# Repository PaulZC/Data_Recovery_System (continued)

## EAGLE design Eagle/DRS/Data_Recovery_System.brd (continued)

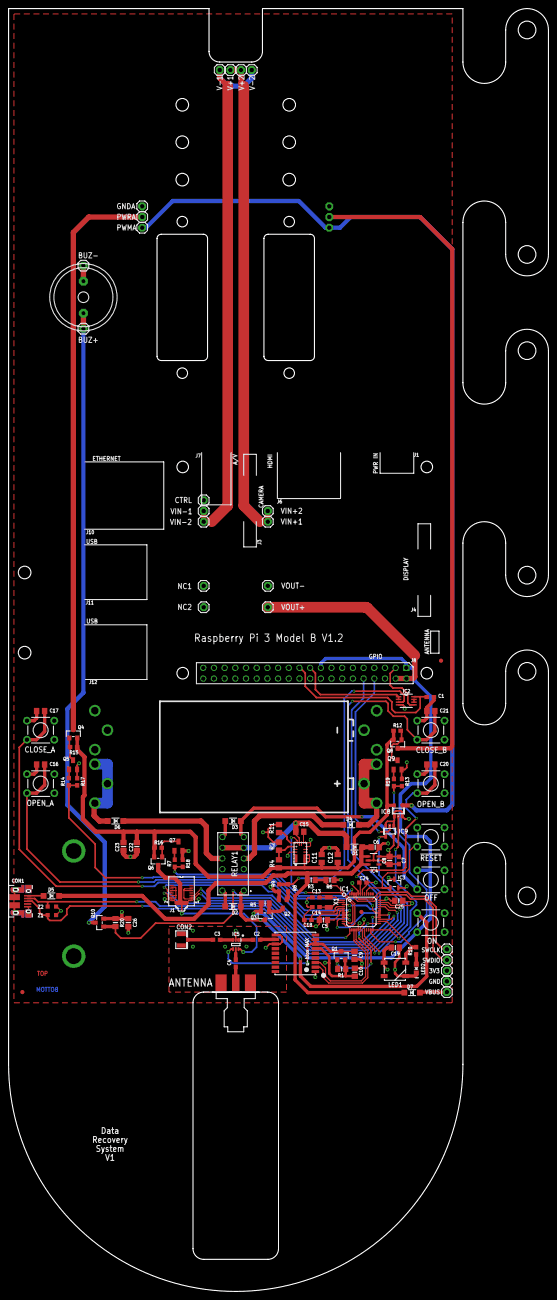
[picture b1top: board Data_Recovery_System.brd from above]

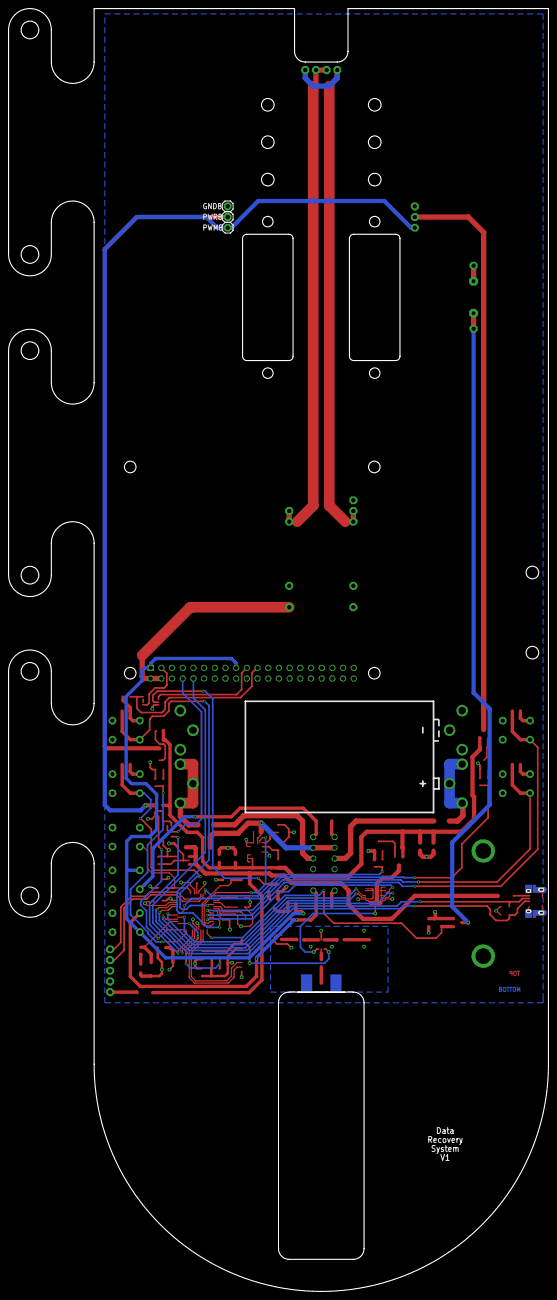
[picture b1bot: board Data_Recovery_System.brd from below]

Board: 4 copper layers, 128.3 x 304.8 mm, 123 parts (4 on the bottom side), 76 nets.

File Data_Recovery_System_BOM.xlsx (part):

Part | X | Y | Angle | Package | Value | Manufacturer | Manufacturer Part No | Farnell Part No | Mouser Part No | McMaster Part No | Description | Alternative Part
Dimensions | 107.95 | 304.80 |  |  |  |  |  |  |  |  | Excludes snap-off servo linkage pieces
Fiducials - for solder paste mask alignment:
FD1 | 3.28 | 71.12 | 0 |  |  |  |  |  |  |  | Fiducial 1mm
FD2 | 102.75 | 149.86000000000001 | 0 |  |  |  |  |  |  |  | Fiducial 1mm
Surface Mount Components:
C1 | 100.2 | 141.22 | 0 | 0603 | 1uF | Walsin | 0603X105K100CT | 2496916 |  |  | MultiLayer Ceramic Capacitor; 1uF; 10V; 0603; X5R | 1uF 50V ±10% 0603 Samsung
C2 | 58.93 | 83.57 | 0 | 0603 | 120pF | Walsin | 0603B121K500CT | 2524820 |  |  | MultiLayer Ceramic Capacitor; 120pF; 50V; 0603
C3 | 49.4 | 83.57 | 180 | 0603 | 120pF | Walsin | 0603B121K500CT | 2524820 |  |  | MultiLayer Ceramic Capacitor; 120pF; 50V; 0603
C4 | 53.98 | 77.98 | 90 | 0603 | 120pF | Walsin | 0603B121K500CT | 2524820 |  |  | MultiLayer Ceramic Capacitor; 120pF; 50V; 0603
C5 | 74.8 | 88.27 | 180 | 0805 | 0.1uF | Walsin | 0805B104K500CT | 2496944 |  |  | MultiLayer Ceramic Capacitor; 0.1uF; 50V; 0805; X7R | 100nF 50V ±10% 0805 Samsung
C6 | 87.1 | 105.54 | 0 | 0805 | 10uF | Walsin | 0805F106Z100CT | 2496998 |  |  | MultiLayer Ceramic Capacitor; 10uF; 10V; 0805 | 10uF 16V ±10% 0805 Samsung
C7 | 92.75 | 102.39 | 270 | 0603 | 1uF | Walsin | 0603X105K100CT | 2496916 |  |  | MultiLayer Ceramic Capacitor; 1uF; 10V; 0603; X5R | 1uF 50V ±10% 0603 Samsung
C8 | 90.53 | 102.39 | 270 | 0805 | 10uF | Walsin | 0805F106Z100CT | 2496998 |  |  | MultiLayer Ceramic Capacitor; 10uF; 10V; 0805 | 10uF 16V ±10% 0805 Samsung
C9 | 82.2 | 79.86 | 270 | 0805 | 0.1uF | Walsin | 0805B104K500CT | 2496944 |  |  | MultiLayer Ceramic Capacitor; 0.1uF; 50V; 0805; X7R | 100nF 50V ±10% 0805 Samsung
C10 | 82.26 | 75.84 | 90 | 0805 | 10uF | Walsin | 0805F106Z100CT | 2496998 |  |  | MultiLayer Ceramic Capacitor; 10uF; 10V; 0805 | 10uF 16V ±10% 0805 Samsung
C11 | 74.400000000000006 | 102.87 | 90 | 0805 | 10nF | Walsin | 0805B103K500CT | 2496939 |  |  | MultiLayer Ceramic Capacitor; 10nF; 50V; 0805; X7R | 10nF 50V ±5% 0805 Samsung
C12 | 78.209999999999994 | 102.87 | 90 | 0805 | 10uF | Walsin | 0805F106Z100CT | 2496998 |  |  | MultiLayer Ceramic Capacitor; 10uF; 10V; 0805 | 10uF 16V ±10% 0805 Samsung
C13 | 73.03 | 93.6 | 180 | 0603 | 12pF | Walsin | 0603N120J500CT | 2496884 |  |  | MultiLayer Ceramic Capacitor; 12pF; 50V; 0603 | 12pF 50V ±5% 0603 Samsung
C14 | 73.03 | 91.31 | 180 | 0603 | 12pF | Walsin | 0603N120J500CT | 2496884 |  |  | MultiLayer Ceramic Capacitor; 12pF; 50V; 0603 | 12pF 50V ±5% 0603 Samsung
C15 | 69.19 | 109.22 | 0 | 0805 | 10uF | Walsin | 0805F106Z100CT | 2496998 |  |  | MultiLayer Ceramic Capacitor; 10uF; 10V; 0805 | 10uF 16V ±10% 0805 Samsung
C16 | 7.62 | 125.2 | 0 | 0805 | 10nF | Walsin | 0805B103K500CT | 2496939 |  |  | MultiLayer Ceramic Capacitor; 10nF; 50V; 0805; X7R | 10nF 50V ±5% 0805 Samsung
C17 | 7.62 | 137.9 | 0 | 0805 | 10nF | Walsin | 0805B103K500CT | 2496939 |  |  | MultiLayer Ceramic Capacitor; 10nF; 50V; 0805; X7R | 10nF 50V ±5% 0805 Samsung
C18 | 71.12 | 88.27 | 180 | 0603 | 1uF | Walsin | 0603X105K100CT | 2496916 |  |  | MultiLayer Ceramic Capacitor; 1uF; 10V; 0603; X5R | 1uF 50V ±10% 0603 Samsung
C19 | 91.89 | 81.69 | 0 | 0805 | 10uF | Walsin | 0805F106Z100CT | 2496998 |  |  | MultiLayer Ceramic Capacitor; 10uF; 10V; 0805 | 10uF 16V ±10% 0805 Samsung
C20 | 100.33 | 125.2 | 0 | 0805 | 10nF | Walsin | 0805B103K500CT | 2496939 |  |  | MultiLayer Ceramic Capacitor; 10nF; 50V; 0805; X7R | 10nF 50V ±5% 0805 Samsung
C21 | 100.33 | 137.9 | 0 | 0805 | 10nF | Walsin | 0805B103K500CT | 2496939 |  |  | MultiLayer Ceramic Capacitor; 10nF; 50V; 0805; X7R | 10nF 50V ±5% 0805 Samsung
C22 | 30.48 | 105.69 | 270 | 0805 | 10uF | Walsin | 0805F106Z100CT | 2496998 |  |  | MultiLayer Ceramic Capacitor; 10uF; 10V; 0805 | 10uF 16V ±10% 0805 Samsung
C23 | 27.3 | 105.69 | 270 | 0805 | 0.1uF | Walsin | 0805B104K500CT | 2496944 |  |  | MultiLayer Ceramic Capacitor; 0.1uF; 50V; 0805; X7R | 100nF 50V ±10% 0805 Samsung
C24 | 84.2 | 97.16 | 0 | 0603 | 1uF | Walsin | 0603X105K100CT | 2496916 |  |  | MultiLayer Ceramic Capacitor; 1uF; 10V; 0603; X5R | 1uF 50V ±10% 0603 Samsung
C25 | 92.71 | 92.84 | 0 | 0805 | 10uF | Walsin | 0805F106Z100CT | 2496998 |  |  | MultiLayer Ceramic Capacitor; 10uF; 10V; 0805 | 10uF 16V ±10% 0805 Samsung
C26 | 28.45 | 87.63 | 270 | 0805 | 10uF | Walsin | 0805F106Z100CT | 2496998 |  |  | MultiLayer Ceramic Capacitor; 10uF; 10V; 0805 | 10uF 16V ±10% 0805 Samsung
CON1 | 2.99 | 92.71 | 270 |  | Micro_USB | Amphenol_FCI | 10103594 | 2293752 |  |  | Amphenol FCI 10103594 Micro USB Type B | A01SB7X4X1B21-167 Micro USB 5S B
CON2 | 41.78 | 83.57 | 0 | uFL | uFL | Hirose | U.FL-R-SMT(01) | 3908021 |  |  | HIROSE U.FL-R-SMT(01); U.FL Coaxial; Straight Jack; 50 ohm
D1 | 82.18 | 105.57 | 180 | SOD-123 | MBR120 | ON SEMICONDUCTOR | MBR120VLSFT1G | 1431044 |  |  | Schottky Rectifier; 20V; 1A; SOD-123
D2 | 53.34 | 91.44 | 180 | SOD-123 | MBR120 | ON SEMICONDUCTOR | MBR120VLSFT1G | 1431044 |  |  | Schottky Rectifier; 20V; 1A; SOD-123
D3 | 53.34 | 111.76 | 180 | SOD-123 | MBR120 | ON SEMICONDUCTOR | MBR120VLSFT1G | 1431044 |  |  | Schottky Rectifier; 20V; 1A; SOD-123
D4 | 81.41 | 110.87 | 0 | SOD-123 | MBR120 | ON SEMICONDUCTOR | MBR120VLSFT1G | 1431044 |  |  | Schottky Rectifier; 20V; 1A; SOD-123
D5 | 10.16 | 93.98 | 180 | SOD-123 | MBR120 | ON SEMICONDUCTOR | MBR120VLSFT1G | 1431044 |  |  | Schottky Rectifier; 20V; 1A; SOD-123
D6 | 25.4 | 111.76 | 180 | SOD-123 | MBR120 | ON SEMICONDUCTOR | MBR120VLSFT1G | 1431044 |  |  | Schottky Rectifier; 20V; 1A; SOD-123
D7 | 95.89 | 70.989999999999995 | 0 | SOD-123 | MBR120 | ON SEMICONDUCTOR | MBR120VLSFT1G | 1431044 |  |  | Schottky Rectifier; 20V; 1A; SOD-123
IC1 | 83.82 | 90.17 | 0 | TQFP48-7X7 | SAMD21G18A-AFT | Atmel / Microchip | SAMD21G18A-AFT |  | 556-ATSAMD21G18A-AFT
IC2 | 94.49 | 140.34 | 0 | SOP65P400X130-8N | SN74LVC2G02DCTR | Texas Instruments | SN74LVC2G02DCTR | 1236358 |  |  | NOR Gate, 2 Input, 32 mA, 1.65 V to 5.5 V, SSOP-8
IC3 | 91.66 | 96.91 | 0 | SOT23-3 | MCP111T-240E/TT | Microchip | MCP111T-240E/TT | 1627192 |  |  | Reset Supervisor; SOT23-3; 2.40V; Open Drain; Active Low
IC4 | 86.72 | 102.39 | 270 | SOT23-5 | SPX3819-3.3 | Exar | SPX3819M5-L-3-3/TR |  | 701-SPX3819M5-L-33TR |  | LDO Voltage Regulator; 500mA; SOT-23-5
IC5 | 53.98 | 82.42 | 270 | SOT65P220X100-6N | AS179-92LF | Skyworks Solutions | AS179-92LF | 1753762 | 873-AS179-92LF |  | Skyworks AS179-92LF RF Switch
IC6 | 68.150000000000006 | 80.34 | 0 |  | MAX-M8Q | u-blox | MAX-M8Q |  |  |  | https://www.u-blox.com/en/product/max-m8-series
IC7 | 69.319999999999993 | 104.32 | 0 | QFN-20 | MPM3610 | MPS | MPM3610AGQV-P |  | 946-MPM3610AGQV-P |  | Switching Voltage Regulator; 21V; 1.2A; DC/DC
IC8 | 92.61 | 114.18 | 0 | SOT23-5 | 74AHCT1G125DBV | Texas Instruments | SN74AHCT1G125DBVR | 1105927 |  |  | Buffer / Line Driver; Single Gate
IC9 | 90.55 | 109.34 | 180 | SOT23-5 | 74AHCT1G125DBV | Texas Instruments | SN74AHCT1G125DBVR | 1105927 |  |  | Buffer / Line Driver; Single Gate
J1 | 41.09 | 94.65 | 270 |  | SS4-10-3.50 | Samtec | SS4-10-3.50-L-D-K-TR | 2085336 |  |  | Samtec SS4-10-3.50-L-D-K-TR
LED1 | 91.8 | 76.52 | 0 |  | WS2812B | Sparkfun / Worldsemi | WS2812B |  | 474-COM-13667 |  | RGB LED with Driver
LED2 | 96.88 | 76.709999999999994 | 180 | 2.0x1.25 | RED | Wurth Electronik | 150080RS75000 | 2322077 | 710-150080RS75000 |  | LED; Red; 20mA; 2V; 2.0x1.25mm
Q1 | 79.03 | 79.8 | 0 | SOT23 | DMG3415U-7 | Diodes Inc. | DMG3415U-7 | 1843688 |  |  | MOSFET; P Channel; SOT23-WIDE
Q2 | 65.150000000000006 | 92.08 | 180 | SOT23 | 2N2222 | Fairchild | MMBT2222A | 9846700 |  |  | Bipolar (BJT) Single Transistor, NPN, 40 V, 350 mW, 1 A
Q3 | 60.96 | 89.28 | 180 | SOT23 | DMG3415U-7 | Diodes Inc. | DMG3415U-7 | 1843688 |  |  | MOSFET; P Channel; SOT23-WIDE
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
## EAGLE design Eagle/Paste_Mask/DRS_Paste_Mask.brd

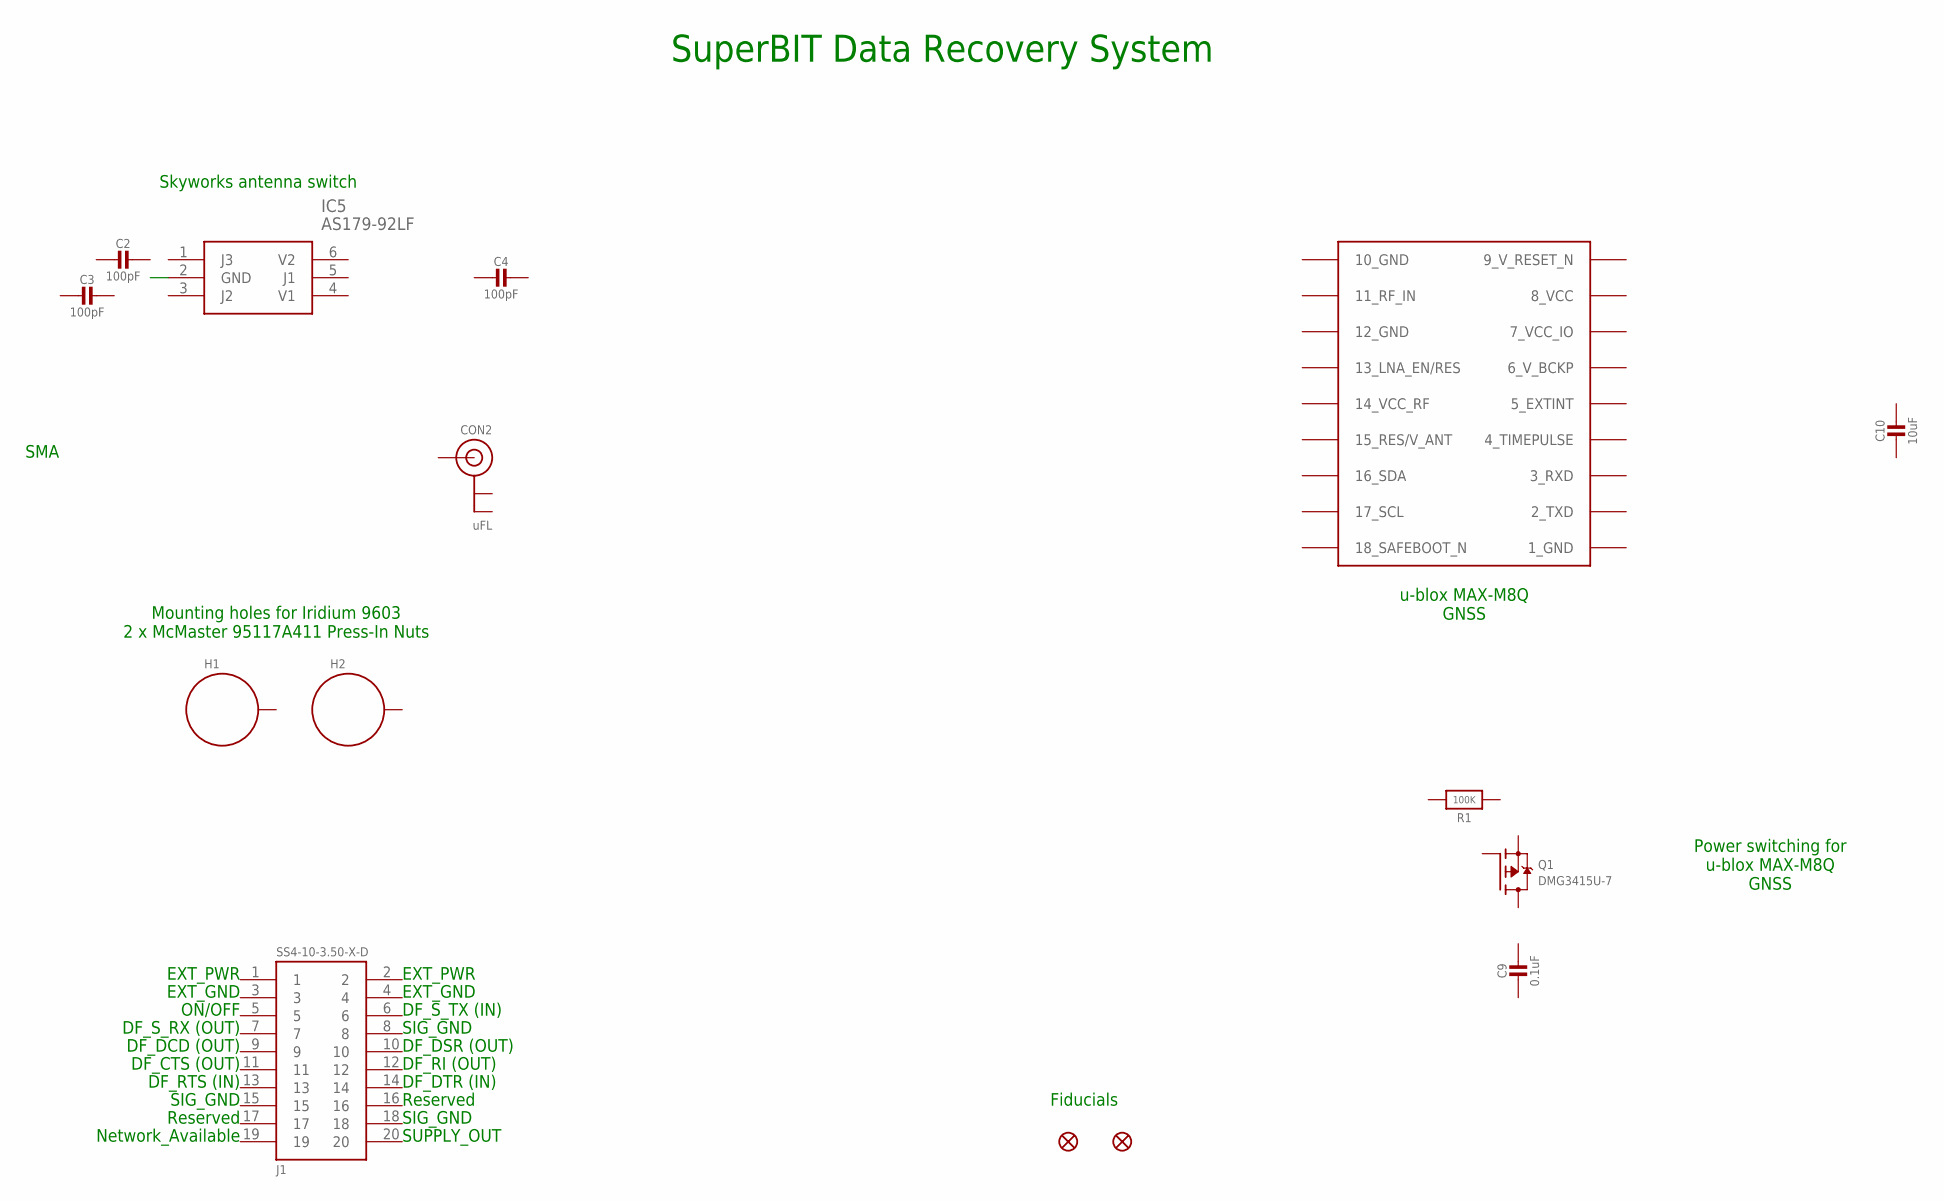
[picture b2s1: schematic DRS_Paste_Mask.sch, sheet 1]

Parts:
C2, C3, C4: 100pF; 0603-NO@1
C9: 0.1uF; 0805-NO@1
C10: 10uF; 0805-NO@1
CON2: uFL; U.FL
FD1, FD2: FIDUCIAL1X2; FIDUCIAL-1X2
H1, H2: STANDOFF_ELECTRICALMCMASTER-95117A411; STANDOFF-ELECTRICAL-MCMASTER-95117A411
IC5: AS179-92LF; SOT65P220X100-6N
IC6: MAX-M8
J1: SS4-10-3.50-X-D
Q1: DMG3415U-7; SOT23-WIDE
R1: 100K; 0805-NO

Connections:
1_GND: IC6.1_GND
7_VCC_IO: IC6.7_VCC_IO
8_VCC: IC6.8_VCC
9_V_RESET_N: IC6.9_RESET_N (9_V_RESET_N)
10_GND: IC6.10_GND
12_GND: IC6.12_GND

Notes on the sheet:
Mounting holes for Iridium 9603 2 x McMaster 95117A411 Press-In Nuts
SuperBIT Data Recovery System
EXT_PWR
EXT_GND
ON/OFF
DF_S_RX (OUT)
DF_DCD (OUT)
DF_CTS (OUT)
DF_RTS (IN)
SIG_GND
Reserved
Network_Available
DF_S_TX (IN)
DF_DSR (OUT)
DF_RI (OUT)
DF_DTR (IN)
SUPPLY_OUT
Fiducials
u-blox MAX-M8Q GNSS
Power switching for u-blox MAX-M8Q GNSS
Skyworks antenna switch
SMA

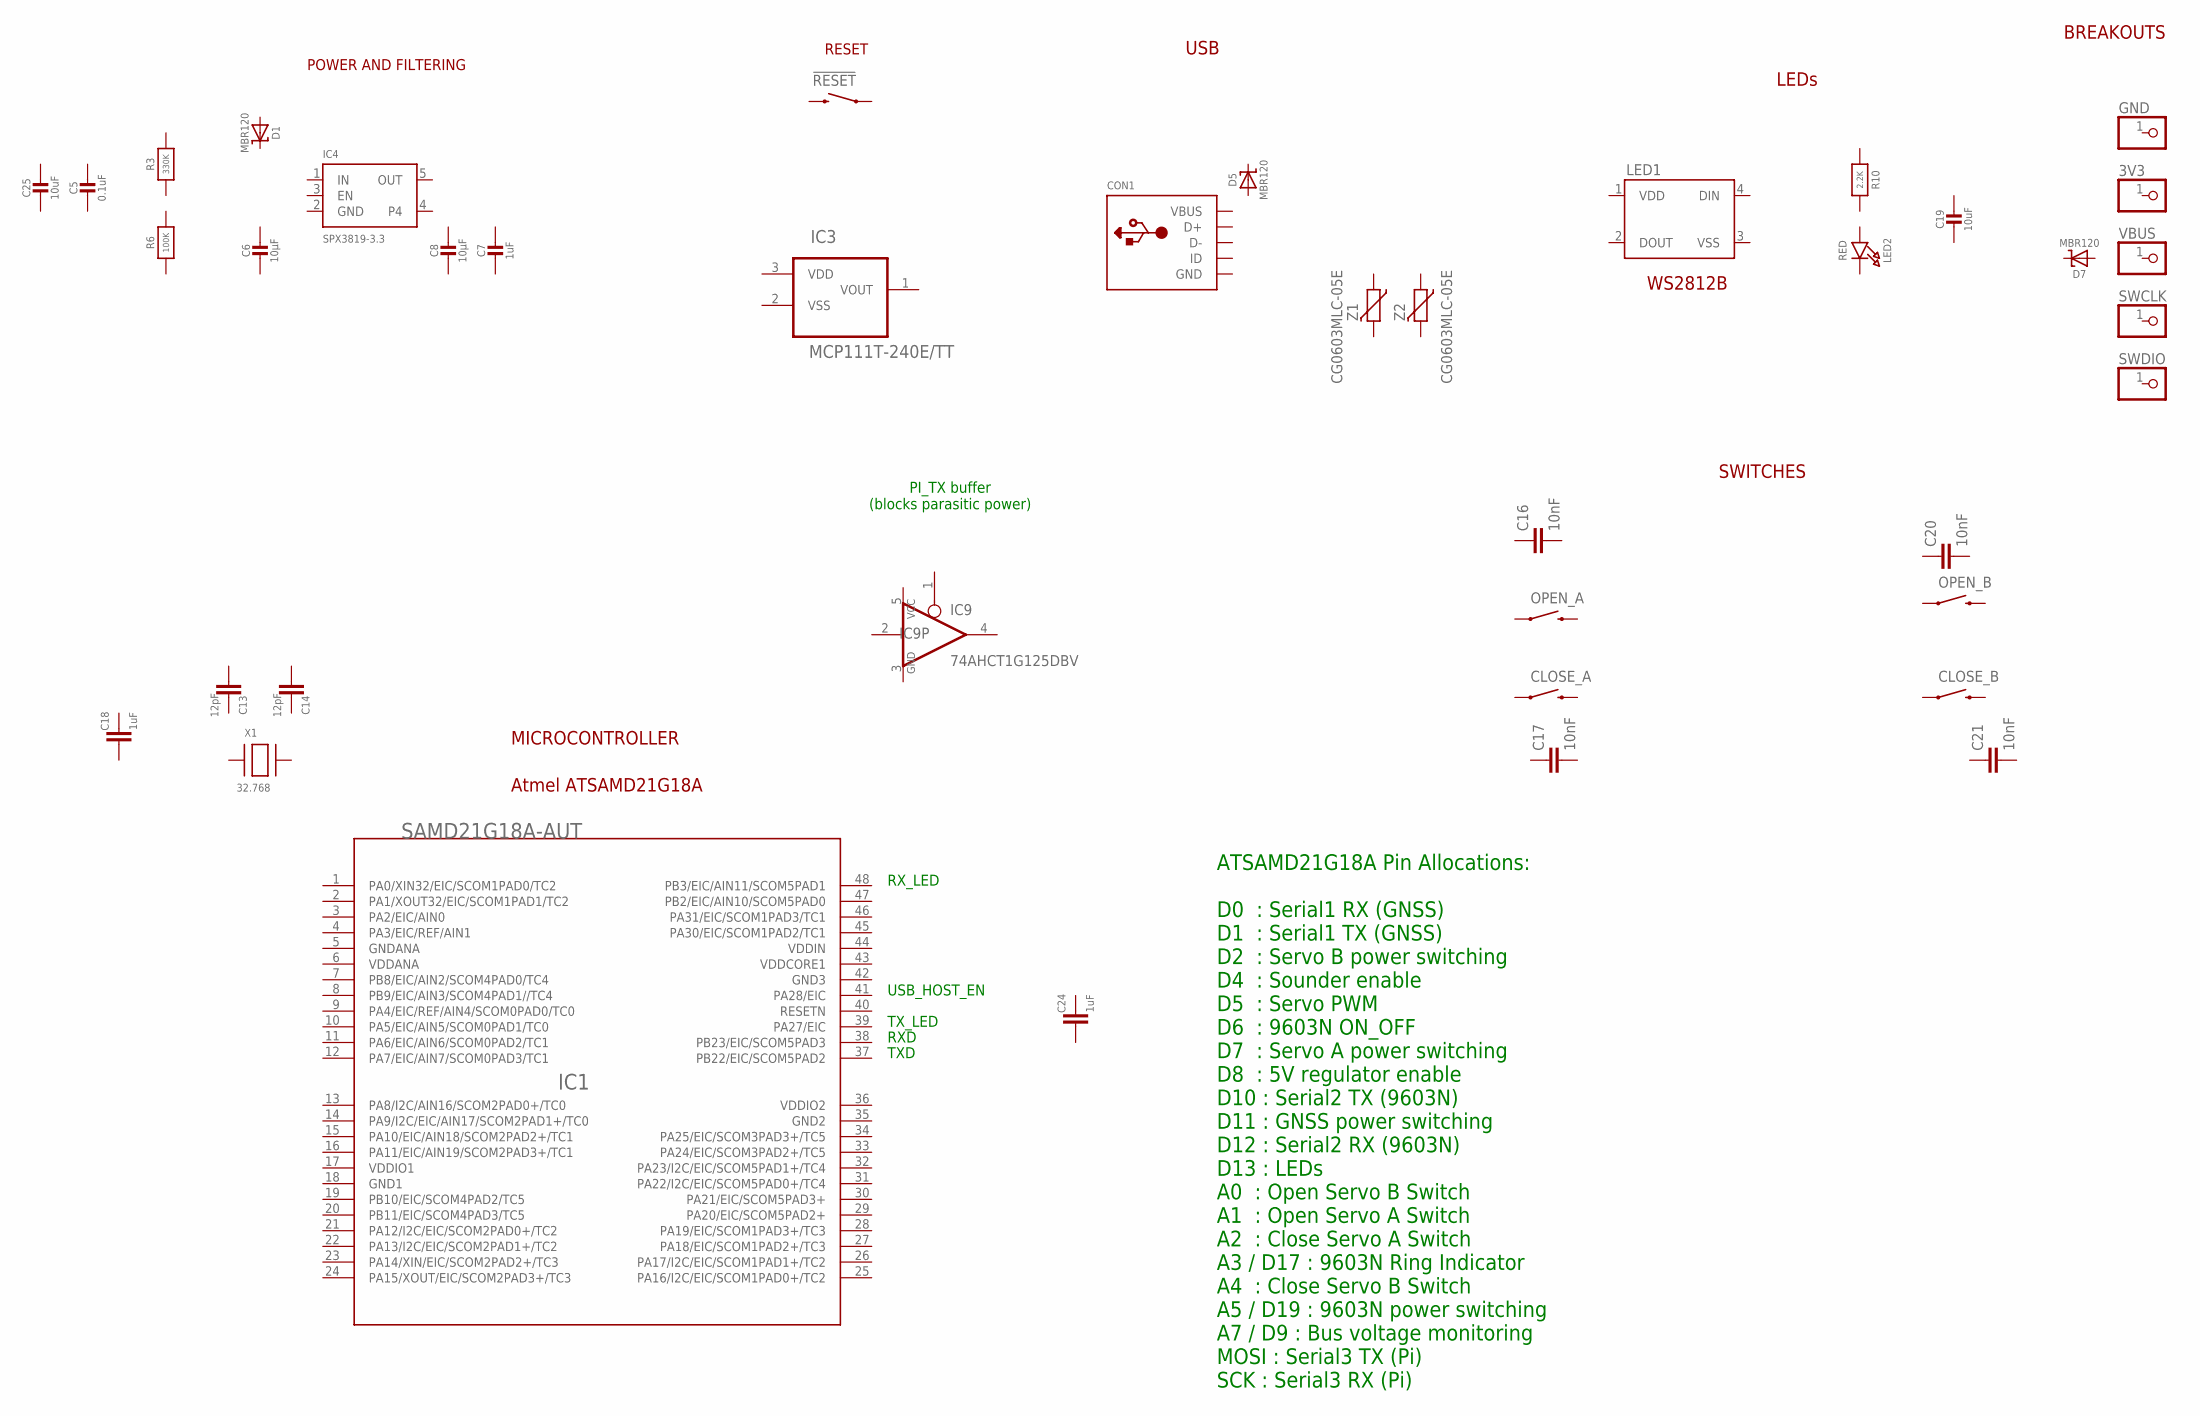
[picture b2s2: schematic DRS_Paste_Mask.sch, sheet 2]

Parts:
3V3: PINHD-1X1; 1X01
!RESET: SWITCH-MOMENTARY-2PTH; TACTILE-PTH
C5: 0.1uF; 0805-NO@1
C6, C8: 10µF; 0805-NO@1
C7: 1uF; 0603-NO@1
C13, C14: 12pF; C0603
C16, C17, C20, C21: 10nF; C0805
C18, C24: 1uF; C0603
C19, C25: 10uF; 0805-NO@1
CLOSE_A: SWITCH-MOMENTARY-2PTH; TACTILE-PTH
CLOSE_B: SWITCH-MOMENTARY-2PTH; TACTILE-PTH
CON1: MICROBUILDER_USBFCI_10103594_CORRECTED; MICROBUILDER_FCI_10103594_CORRECTED
D1, D5, D7: MBR120; SOD-123
GND: PINHD-1X1; 1X01
IC1: SAMD21G18A-AUT; TQFP48-7X7
IC3: MCP111T-240E/TT; SOT95P237X112-3N; MPN MCP111T-240E/TT
IC4: SPX3819-3.3; SOT23-5
IC9: 74AHCT1G125DBV; SOT23-5
LED1: WS2812B
LED2: RED; CHIPLED_0805_NOOUTLINE
OPEN_A: SWITCH-MOMENTARY-2PTH; TACTILE-PTH
OPEN_B: SWITCH-MOMENTARY-2PTH; TACTILE-PTH
R3: 330K; 0805-NO
R6: 100K; 0805-NO
R10: 2.2K; 0603-NO
SWCLK: PINHD-1X1; 1X01
SWDIO: PINHD-1X1; 1X01
VBUS: PINHD-1X1; 1X01
X1: 32.768; XTAL3215
Z1, Z2: CG0603MLC-05E; CT/CN0603

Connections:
GND: CON1.BASE@1 (GND), CON1.BASE@2 (GND), CON1.GND, CON1.SPRT@1 (GND), CON1.SPRT@2 (GND), CON1.SPRT@3 (GND), CON1.SPRT@4 (GND), IC4.2 (GND), IC9.3 (GND); also elsewhere on the board
GND1: IC1.18 (GND1)
GND2: IC1.35 (GND2)
GND3: IC1.42 (GND3)
GNDANA: IC1.5 (GNDANA)
IN: IC4.1 (IN)
VBUS: CON1.VBUS
VCC: IC9.5 (VCC); also elsewhere on the board
VDD: IC3.3 (VDD), LED1.1 (VDD)
VDDANA: IC1.6 (VDDANA)
VDDIN: IC1.44 (VDDIN)
VDDIO1: IC1.17 (VDDIO1)
VDDIO2: IC1.36 (VDDIO2)
VSS: IC3.2 (VSS), LED1.3 (VSS)

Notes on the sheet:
MICROCONTROLLER
USB_HOST_EN
TXD
RXD
TX_LED
RX_LED
Atmel ATSAMD21G18A
POWER AND FILTERING
RESET
USB
BREAKOUTS
LEDs
WS2812B
SWITCHES
ATSAMD21G18A Pin Allocations: D0 : Serial1 RX (GNSS) D1 : Serial1 TX (GNSS) D2 : Servo B power switching D4 : Sounder enable D5 : Servo PWM D6 : 9603N ON_OFF D7 : Servo A power switching D8 : 5V regulator enable D10 : Serial2 TX (9603N) D11 : GNSS power switching D12 : Serial2 RX (9603N) D13 : LEDs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
PI_TX buffer (blocks parasitic power)

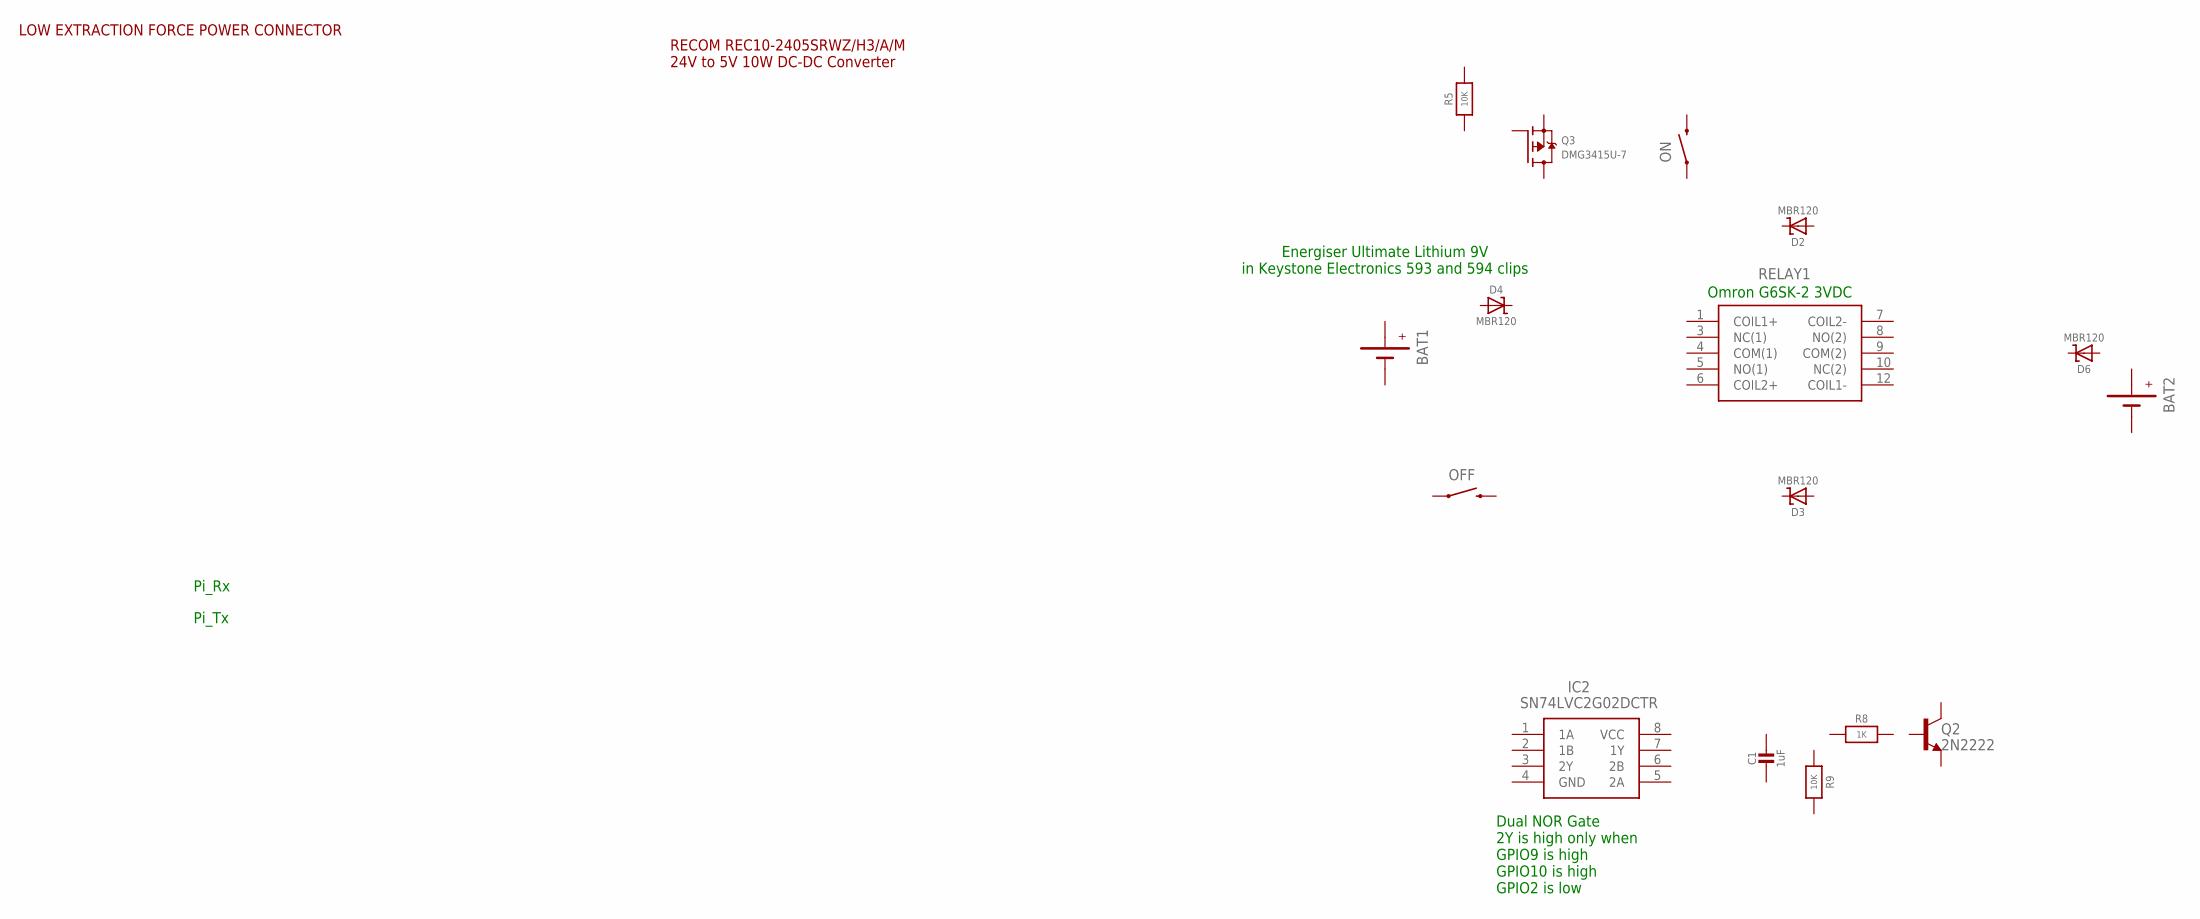
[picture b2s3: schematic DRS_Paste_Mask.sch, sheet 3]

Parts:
BAT1, BAT2: BATTERYBATTERY-9V-KEYSTONE-593-594; BATTERY-9V-KEYSTONE-593-594
C1: 1uF; 0603-NO@1
D2, D3, D4, D6: MBR120; SOD-123
IC2: SN74LVC2G02DCTR; SOP65P400X130-8N
OFF: SWITCH-MOMENTARY-2PTH; TACTILE-PTH
ON: SWITCH-MOMENTARY-2PTH; TACTILE-PTH
Q2: 2N2222; SOT23-BEC
Q3: DMG3415U-7; SOT23-WIDE
R5: 10K; 0805-NO
R8: 1K; 0603-NO
R9: 10K; 0603-NO
RELAY1: G6SK-2_DC5; G6SK2DC5

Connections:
+: BAT1.PWR (+), BAT1.PWR1 (+), BAT1.PWR2 (+), BAT2.PWR (+), BAT2.PWR1 (+), BAT2.PWR2 (+)
-: BAT1.GND (-), BAT1.GND1 (-), BAT1.GND2 (-), BAT2.GND (-), BAT2.GND1 (-), BAT2.GND2 (-)

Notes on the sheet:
Omron G6SK-2 3VDC
Energiser Ultimate Lithium 9V in Keystone Electronics 593 and 594 clips
LOW EXTRACTION FORCE POWER CONNECTOR
RECOM REC10-2405SRWZ/H3/A/M 24V to 5V 10W DC-DC Converter
Dual NOR Gate 2Y is high only when GPIO9 is high GPIO10 is high GPIO2 is low
Pi_Tx
Pi_Rx

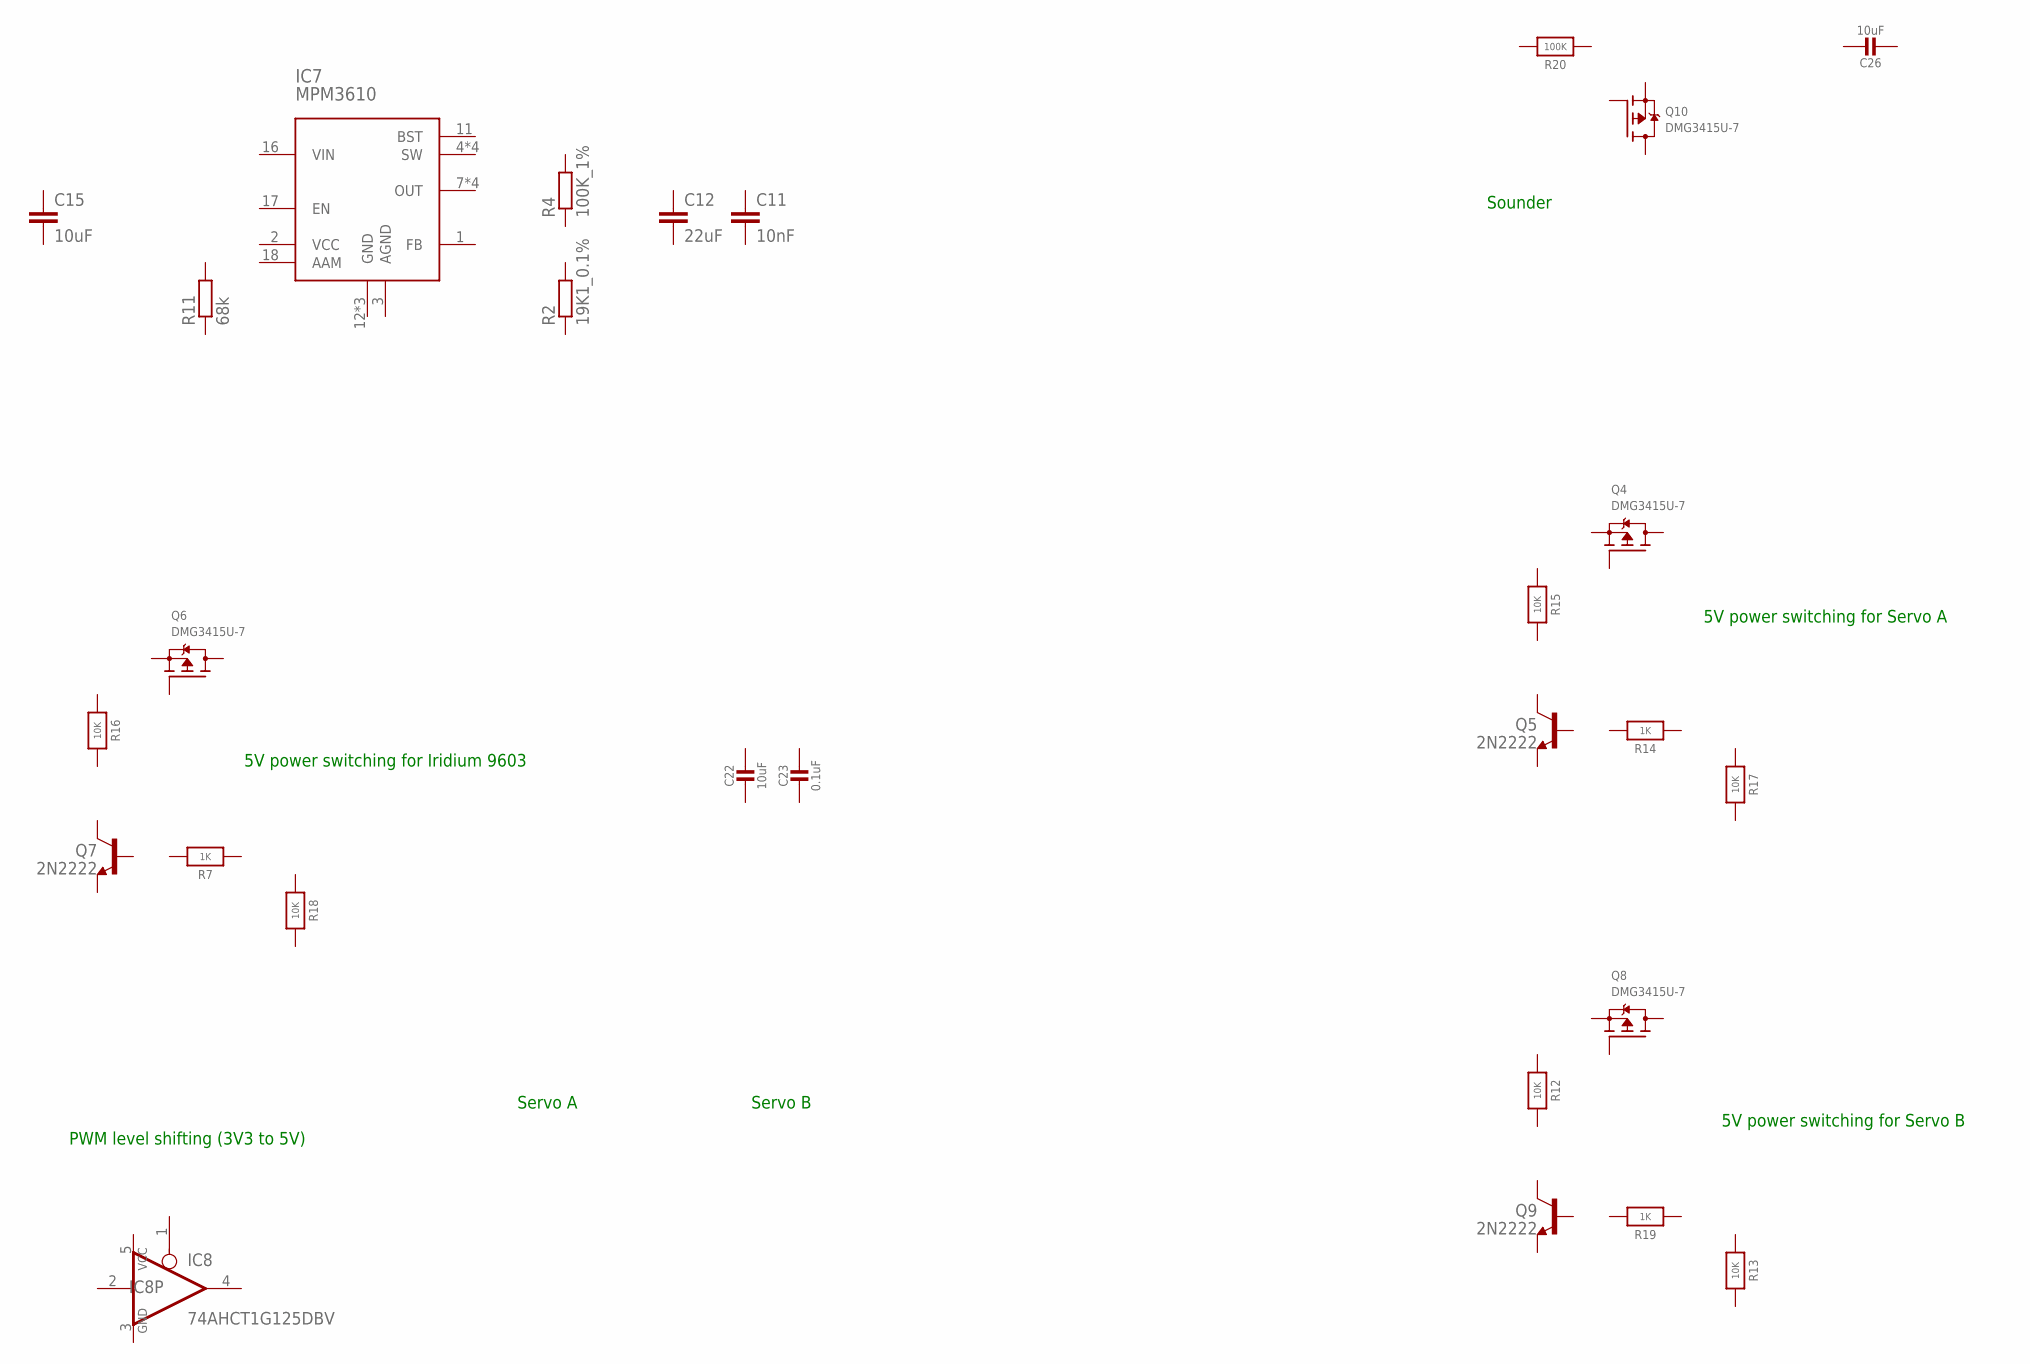
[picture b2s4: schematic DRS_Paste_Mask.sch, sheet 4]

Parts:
C11: 10nF; C0805
C12: 22uF; C0805
C15: 10uF; C0805
C22, C26: 10uF; 0805-NO@1
C23: 0.1uF; 0805-NO@1
IC7: MPM3610; QFN-20
IC8: 74AHCT1G125DBV; SOT23-5
Q4, Q6, Q8, Q10: DMG3415U-7; SOT23-WIDE
Q5, Q7, Q9: 2N2222; SOT23-BEC
R2: 19K1_0.1%; R0805
R4: 100K_1%; R0805
R7, R14, R19: 1K; 0603-NO
R11: 68k; R0805
R12, R13, R15, R16, R17, R18: 10K; 0603-NO
R20: 100K; 0805-NO

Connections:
GND: IC8.3 (GND); also elsewhere on the board
VCC: IC8.5 (VCC); also elsewhere on the board

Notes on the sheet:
Servo A
Servo B
5V power switching for Servo A
5V power switching for Servo B
5V power switching for Iridium 9603
PWM level shifting (3V3 to 5V)
Sounder

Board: 4 copper layers, 99 parts (1 on the bottom side), 6 nets, no tracks yet.

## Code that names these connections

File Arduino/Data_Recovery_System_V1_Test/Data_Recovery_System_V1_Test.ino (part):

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// D1  : Serial1 TX (GNSS)
// D2  : Servo B power switching
// D4 / PA08 / TCC1WO2 : Sounder enable
// D5 / PA15 / TCC0WO5 : Servo PWM
// D6  : 9603N ON_OFF
// D7  : Servo A power switching
// D8  : 5V regulator enable
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static const int ServoB = 2; // Servo B Enable (Pull high to enable the servo)
static const int Sounder = 4; // Sounder Enable (Pull low to enable the sounder)
const uint8_t pwmPin = 5;
static const int IridiumSleepPin = 6; // Iridium Sleep connected to D6
static const int ServoA = 7; // Servo A Enable (Pull high to enable the servo)
static const int enable5V = 8; // Enable the MPM3610 5V regulator (Pull high to enable 5V)
static const int GPS_EN = 11; // GNSS Enable on pin D11 (Pull low to enable the GNSS)
static const int ledPin = 13; // WB2812B + Red LED on pin D13
static const int openSwitchB = 14;
static const int openSwitchA = 15;
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  
  pinMode(pwmPin, OUTPUT); // Redundant?

  //pinMode(IridiumSleepPin, OUTPUT); // Iridium 9603N Sleep Pin
  //digitalWrite(IridiumSleepPin, LOW); // Disable the Iridium 9603
  pinMode(ringIndicator, INPUT); // Define an input for the Iridium 9603 Ring Indicator

  pixels.begin(); // This initializes the NeoPixel library.
  delay(100); // Seems necessary to make the NeoPixel start reliably 
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  while (GCLK->STATUS.bit.SYNCBUSY);              // Wait for synchronization

  // Enable the port multiplexer for the PWM channel: timer TCC0 outputs
  // Digital pin 5 is PA15
  // PA15 Peripheral E is TC3WO1
  // PA15 Peripheral F is TCC0WO5
  // PORT->Group[g_APinDescription[pwmPin].ulPort].PINCFG[g_APinDescription[pwmPin].ulPin].bit.PMUXEN = 1;
  PORT->Group[PORTA].PINCFG[15].bit.PMUXEN = 1; // Set the PMUXEN bit in the PINCFG register to allow TCC) to control the pin
  // Connect the TCC0 timer to the port outputs - port pins are paired odd PMUO and even PMUXE
  // F & E specify the timers: TCC0, TCC1 and TCC2
  // Digital pin 5 is PA15 (odd). PA14 (even) is Digital pin 2. So need to refer to pin 2 ODD!
  // PORT->Group[g_APinDescription[2].ulPort].PMUX[g_APinDescription[2].ulPin >> 1].reg = PORT_PMUX_PMUXO_F;
  PORT->Group[PORTA].PMUX[14 >> 1].reg = PORT_PMUX_PMUXO_F; // Set the odd nibble to peripheral F

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
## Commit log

2019-06-02 Work in progress
2019-06-14 More added - but still work in progress
2019-06-14 Minor additions
2019-06-14 Added PCB.md
2023-10-02 New Zealand SPB additions - files for 3D printing
    Inventor or SCAD files for 3D printing/milling the adapted case, crown release mechanism, and heatsink used in the 2023 flight from New Zealand.
2023-11-17 Update README.md - use relative links
